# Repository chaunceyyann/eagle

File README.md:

EAGLE
=====
All my eagle projects and libraries can be found here.

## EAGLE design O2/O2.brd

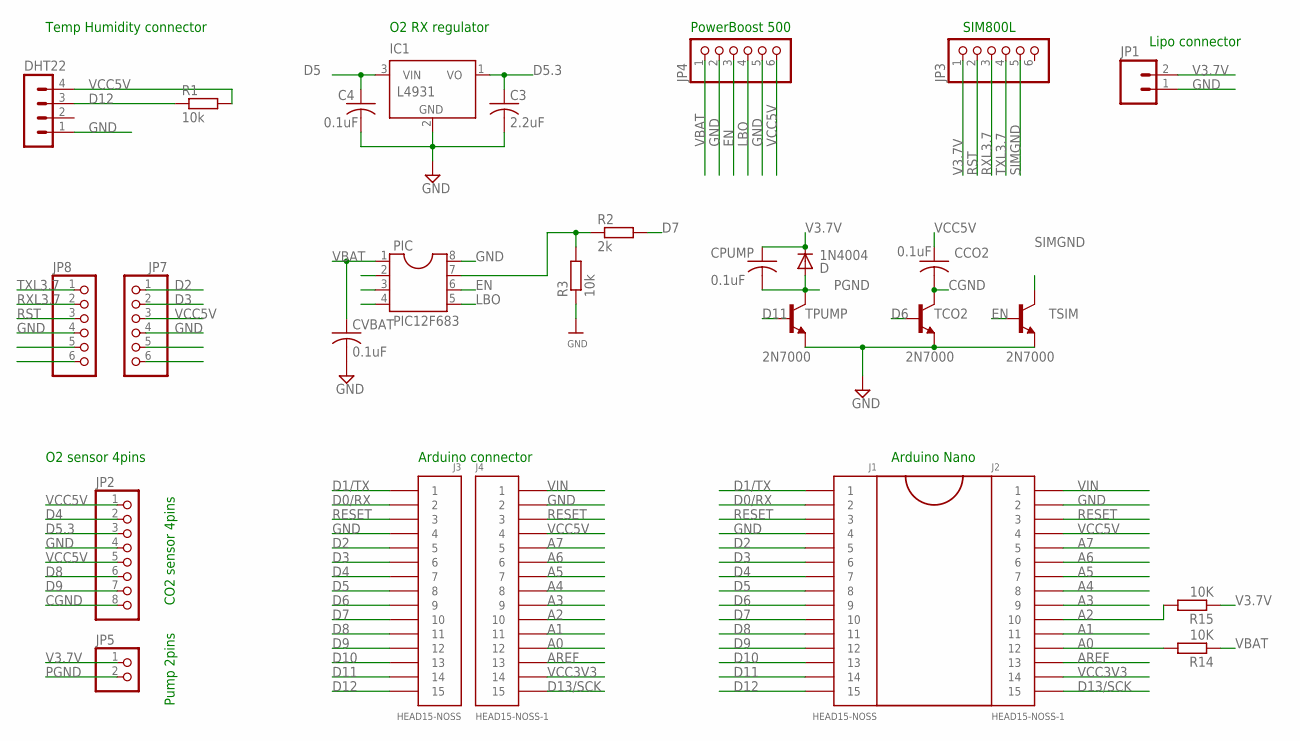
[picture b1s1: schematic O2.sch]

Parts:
C3: 2.2uF; C025-030X050
C4: 0.1uF; C025-030X050
CCO2: 0.1uF; C025-030X050
CPUMP: 0.1uF; C025-030X050
CVBAT: 0.1uF; C025-030X050
D: 1N4004; DO41-10
DHT22: MA04-1
IC1: L4931; TO92
J1, J3: HEAD15-NOSS
J2, J4: HEAD15-NOSS-1
JP1: M023.5MM; SCREWTERMINAL-3.5MM-2
JP2: PINHD-1X8BIG; 1X08-BIG
JP3, JP4, JP7, JP8: PINHD-1X6CB; 1X06-CLEANBIG
JP5: PINHD-1X2; 1X02
PIC: PIC12F683; SOCKET-08
R1, R3: 10k; 0204/5
R2: 2k; 0204/5
R14, R15: 10K; 0204/5
TCO2: 2N7000; TO92-EBC-OVAL
TPUMP: 2N7000; TO92-EBC-OVAL
TSIM: 2N7000; TO92-EBC-OVAL

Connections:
A0: J2.12, J4.12, R14.2
A1: J2.11, J4.11
A2: J2.10, J4.10, R15.2
A3: J2.9, J4.9
A4: J2.8, J4.8
A5: J2.7, J4.7
A6: J2.6, J4.6
A7: J2.5, J4.5
AREF: J2.13, J4.13
CGND: CCO2.2, JP2.8, TCO2.C
D0/RX: J1.2, J3.2
D1/TX: J1.1, J3.1
D2: J1.5, J3.5, JP7.1
D3: J1.6, J3.6, JP7.2
D4: J1.7, J3.7, JP2.2
D5: C4.1, IC1.3 (VIN), J1.8, J3.8
D5.3: C3.1, IC1.1 (VO), JP2.3
D6: J1.9, J3.9, TCO2.B
D7: J1.10, J3.10, R2.2
D8: J1.11, J3.11, JP2.6
D9: J1.12, J3.12, JP2.7
D10: J1.13, J3.13
D11: J1.14, J3.14, TPUMP.B
D12: DHT22.3, J1.15, J3.15, R1.1
D13/SCK: J2.15, J4.15
EN: JP4.3, PIC.6, TSIM.B
GND: C3.2, C4.2, CVBAT.2, DHT22.1, IC1.2 (GND), J1.4, J2.2, J3.4, J4.2, JP1.1, JP2.4, JP4.2, JP4.5, JP7.4, JP8.4, PIC.8, R3.1, TCO2.E, TPUMP.E, TSIM.E
LBO: JP4.4, PIC.5
unnamed: PIC.7, R2.1, R3.2
PGND: CPUMP.2, D.A, JP5.2, TPUMP.C
RESET: J1.3, J2.3, J3.3, J4.3
RST: JP3.2, JP8.3
RXL3.7: JP3.3, JP8.2
SIMGND: JP3.5, TSIM.C
TXL3.7: JP3.4, JP8.1
V3.7V: CPUMP.1, D.C, JP1.2, JP3.1, JP5.1, R15.1
VBAT: CVBAT.1, JP4.1, PIC.1, R14.1
VCC3V3: J2.14, J4.14
VCC5V: CCO2.1, DHT22.4, J2.4, J4.4, JP2.1, JP2.5, JP4.6, JP7.3, R1.2
VIN: J2.1, J4.1

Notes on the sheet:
O2 RX regulator
O2 sensor 4pins
Temp Humidity connector
Lipo connector
PowerBoost 500
Arduino Nano
Arduino connector
Pump 2pins
CO2 sensor 4pins
SIM800L

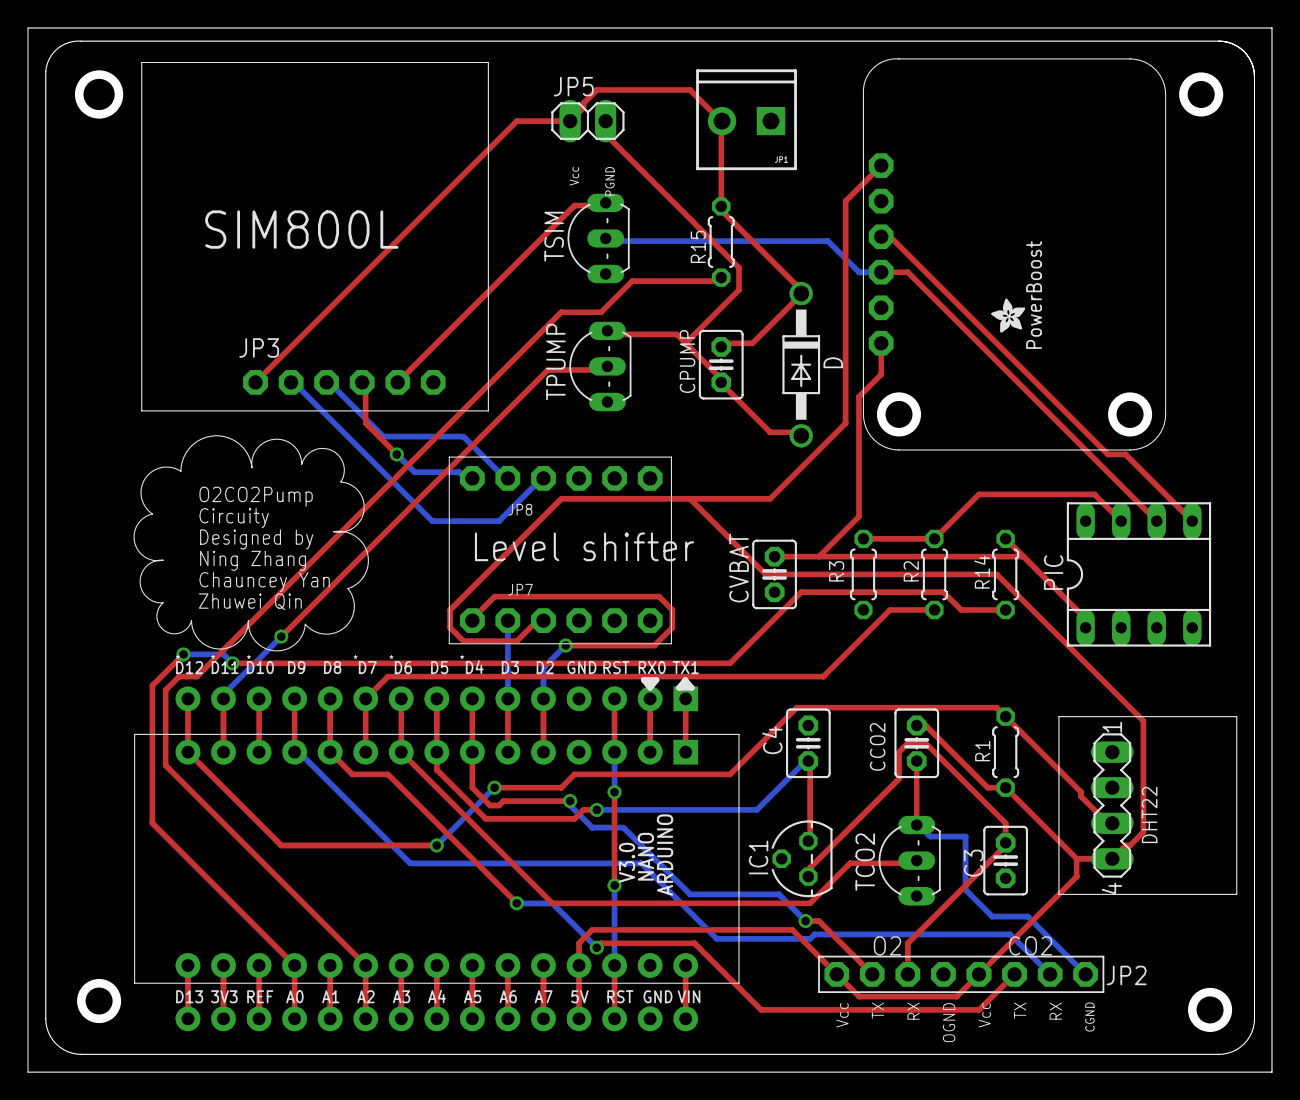
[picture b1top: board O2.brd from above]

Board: 2 copper layers, 88.9 x 74.6 mm, 29 parts (0 on the bottom side), 40 nets.

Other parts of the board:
U$34: ADAFRUIT_2.5MM

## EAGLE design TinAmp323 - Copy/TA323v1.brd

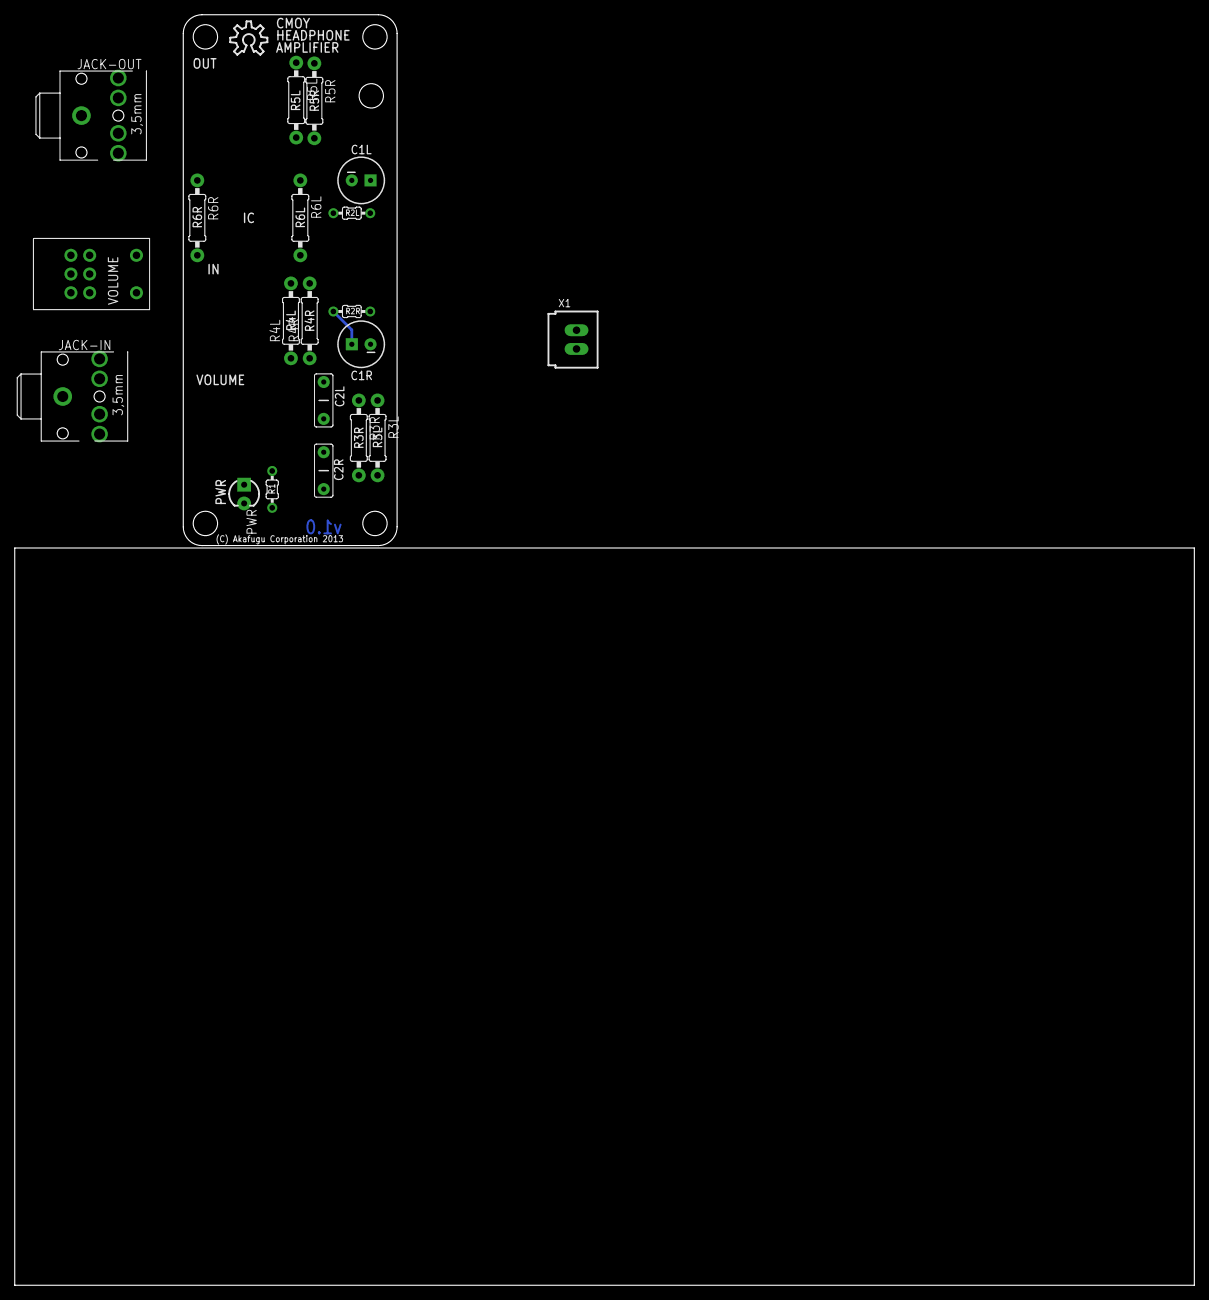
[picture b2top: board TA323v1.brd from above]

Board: 2 copper layers, 160.0 x 172.3 mm, 26 parts (0 on the bottom side), 15 nets.

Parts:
C1L, C1R: 220uF; CPOL-RADIAL-6.3MM
C2L, C2R: 0.1uF; CAP-PTH-VIMA-MKS2C031001A00KSSD
JACK-IN: STEREOJACK; STX3100
JACK-OUT: STEREOJACK; STX3100
JP1, JP2, JP3, JP4, JP5: STAND-OFF
PWR: LED3MM-MINUS
R1: 10k; 1/6W-RES-OUTLINE
R2L, R2R: 4.7k; 1/6W-RES-OUTLINE
R3L, R3R: 100k; 1/4W-RES-OUTLINE
R4L, R4R: 2k; 1/4W-RES-OUTLINE
R5L, R5R: 10k; 1/4W-RES-OUTLINE
R6L, R6R: 47R; 1/4W-RES-OUTLINE
U$1: OSHW-LOGO-OUTLINE
VOLUME: 10k; ALPS_RK0971221Z0X
X1: C-GRID-02-70543; 70543-02

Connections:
+9V: C1R.1, R1.2, R2R.2, VOLUME.S2
GND: C1L.2, JACK-IN.1, JACK-OUT.1, PWR.K, R2L.1, R3L.P$1, R3R.P$1, R4L.P$1, R4R.P$1, VOLUME.G1, VOLUME.G2, X1.1
INPUT-L: JACK-IN.2, VOLUME.I1
INPUT-R: JACK-IN.5, VOLUME.I2
L+: C2L.2, R3L.P$2
L-: R4L.P$2, R5L.P$2
unnamed: PWR.A, R1.1
unnamed: VOLUME.S1, X1.2
unnamed: C1L.1, C1R.2, R2L.2, R2R.1
OUTPUT-L: JACK-OUT.2, R5L.P$1, R6L.P$1
OUTPUT-R: JACK-OUT.5, R5R.P$1, R6R.P$1
R+: C2R.2, R3R.P$2
R-: R4R.P$2, R5R.P$2
VOLUME-OUT-L: C2L.1, VOLUME.O1
VOLUME-OUT-R: C2R.1, VOLUME.O2

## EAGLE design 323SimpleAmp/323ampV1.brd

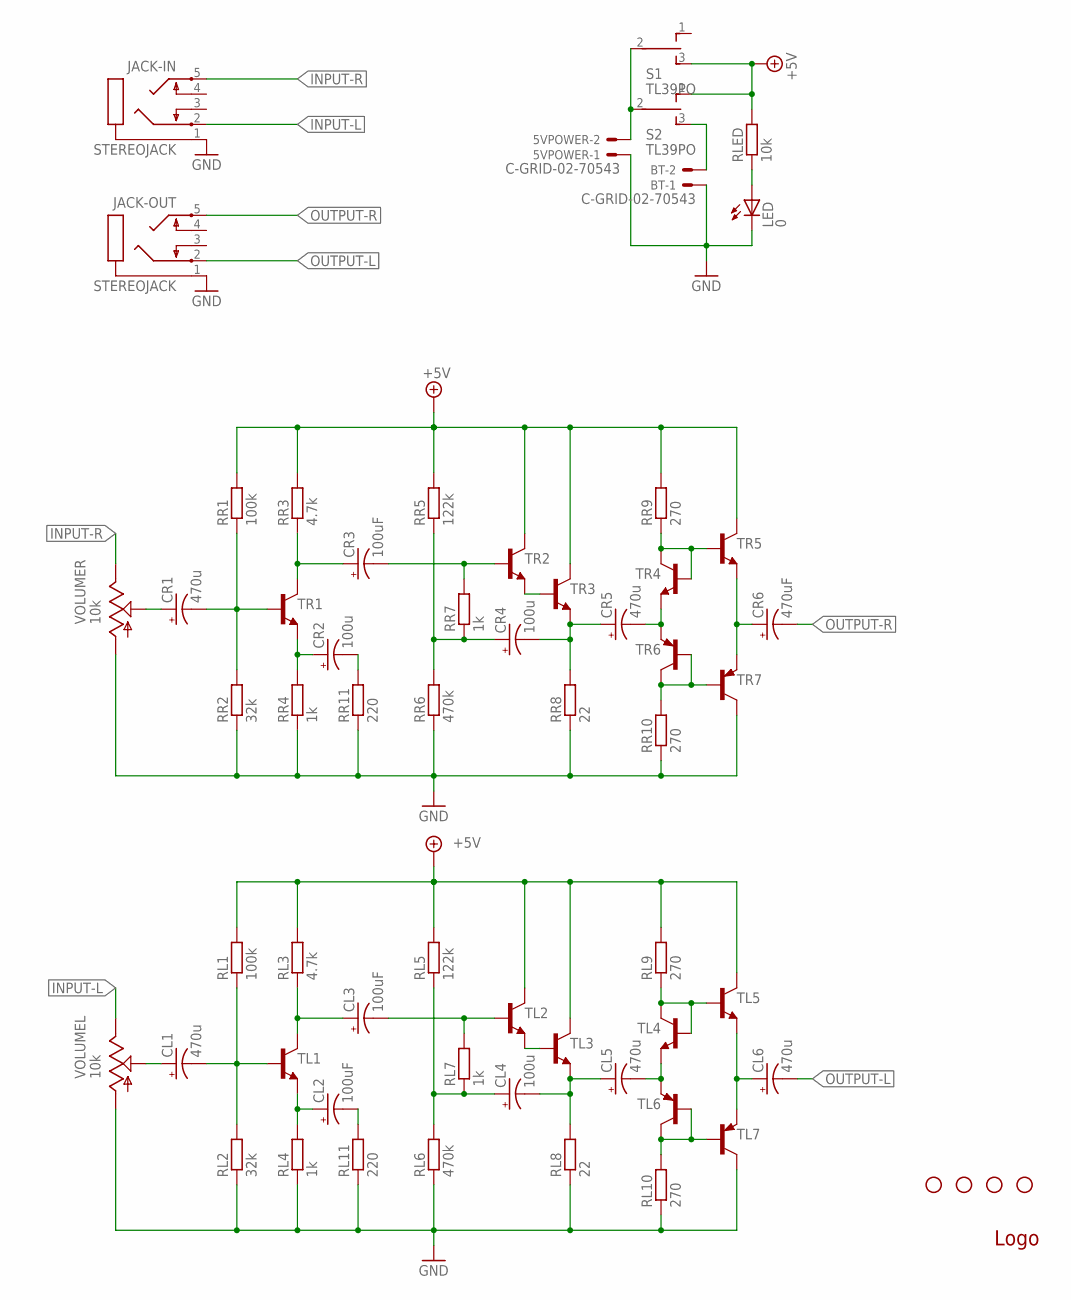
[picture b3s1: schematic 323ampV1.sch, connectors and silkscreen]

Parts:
5VPOWER: C-GRID-02-70543; 70543-02
BT: C-GRID-02-70543; 70543-02
CL1, CL5, CL6: 470u; E2,5-6
CL2, CL3: 100uF; E2,5-6
CL4: 100u; E2,5-6
CR1, CR5: 470u; E2,5-6
CR2, CR4: 100u; E2,5-6
CR3: 100uF; E2,5-6
CR6: 470uF; E2,5-6
JACK-IN: STEREOJACK; STX3100
JACK-OUT: STEREOJACK; STX3100
JP2, JP3, JP4, JP5: STAND-OFF
LED: 0; LED3MM-MINUS
RL1: 100k; 0204/7
RL2: 32k; 0204/7
RL3: 4.7k; 0204/7
RL4, RL7: 1k; 0204/7
RL5: 122k; 0204/7
RL6: 470k; 0204/7
RL8: 22; 0204/7
RL9, RL10: 270; 0204/7
RL11: 220; 0204/7
RLED: 10k; 0204/7
RR1: 100k; 0204/7
RR2: 32k; 0204/7
RR3: 4.7k; 0204/7
RR4, RR7: 1k; 0204/7
RR5: 122k; 0204/7
RR6: 470k; 0204/7
RR8: 22; 0204/7
RR9, RR10: 270; 0204/7
RR11: 220; 0204/7
S1, S2: TL39PO; TL3XPO
TL1, TL2, TL3, TL4, TL5: 2N4401-NPN-TO92-EBC; TO92-EBC
TL6, TL7: 2N4403-PNP-TO92-EBC; TO92-EBC
TR1, TR2, TR3, TR4, TR5: 2N4401-NPN-TO92-EBC; TO92-EBC
TR6, TR7: 2N4403-PNP-TO92-EBC; TO92-EBC
U$1: OSHW-LOGO-OUTLINE
VOLUME: 10k; ALPS_RK0971221Z0X

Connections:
+5V: RL1.2, RL3.2, RL5.2, RL9.2, RLED.2, RR1.2, RR3.2, RR5.2, RR9.2, S1.3 (S), S2.1 (O), TL2.C, TL3.C, TL5.C, TR2.C, TR3.C, TR5.C
GND: 5VPOWER.1, BT.1, JACK-IN.1, JACK-OUT.1, LED.K (C), RL2.1, RL4.1, RL6.1, RL8.1, RL10.1, RL11.1, RR2.1, RR4.1, RR6.1, RR8.1, RR10.1, RR11.1, TL7.C, TR7.C, VOLUME.G1 (1), VOLUME.G2 (1)
INPUT-L: JACK-IN.2, VOLUME.I1 (3)
INPUT-R: JACK-IN.5, VOLUME.I2 (3)
unnamed: LED.A, RLED.1
unnamed: 5VPOWER.2, S1.2, S2.2
unnamed: TR2.E, TR3.B
unnamed: CR3.+, RR3.1, TR1.C
unnamed: RL9.1, TL4.B, TL4.C, TL5.B
unnamed: CL5.-, TL4.E, TL6.E
unnamed: RL10.2, TL6.B, TL6.C, TL7.B
unnamed: CL6.+, TL5.E, TL7.E
unnamed: CL4.-, CL5.+, RL8.2, TL3.E
unnamed: CL4.+, RL5.1, RL6.2, RL7.1
unnamed: CL3.-, RL7.2, TL2.B
unnamed: CL2.-, RL11.2
unnamed: CL2.+, RL4.2, TL1.E
unnamed: CL1.+, VOLUME.O1 (2)
unnamed: TL2.E, TL3.B
unnamed: CL3.+, RL3.1, TL1.C
unnamed: BT.2, S2.3 (S)
unnamed: RR9.1, TR4.B, TR4.C, TR5.B
unnamed: CR5.-, TR4.E, TR6.E
unnamed: RR10.2, TR6.B, TR6.C, TR7.B
unnamed: CR6.+, TR5.E, TR7.E
unnamed: CR4.-, CR5.+, RR8.2, TR3.E
unnamed: CR4.+, RR5.1, RR6.2, RR7.1
unnamed: CR3.-, RR7.2, TR2.B
unnamed: CR2.-, RR11.2
unnamed: CR2.+, RR4.2, TR1.E
unnamed: CR1.+, VOLUME.O2 (2)
OUTPUT-L: CL6.-, JACK-OUT.2
OUTPUT-R: CR6.-, JACK-OUT.5
R+: CR1.-, RR1.1, RR2.2, TR1.B
R+1: CL1.-, RL1.1, RL2.2, TL1.B
S1: VOLUME.S1
S2: VOLUME.S2

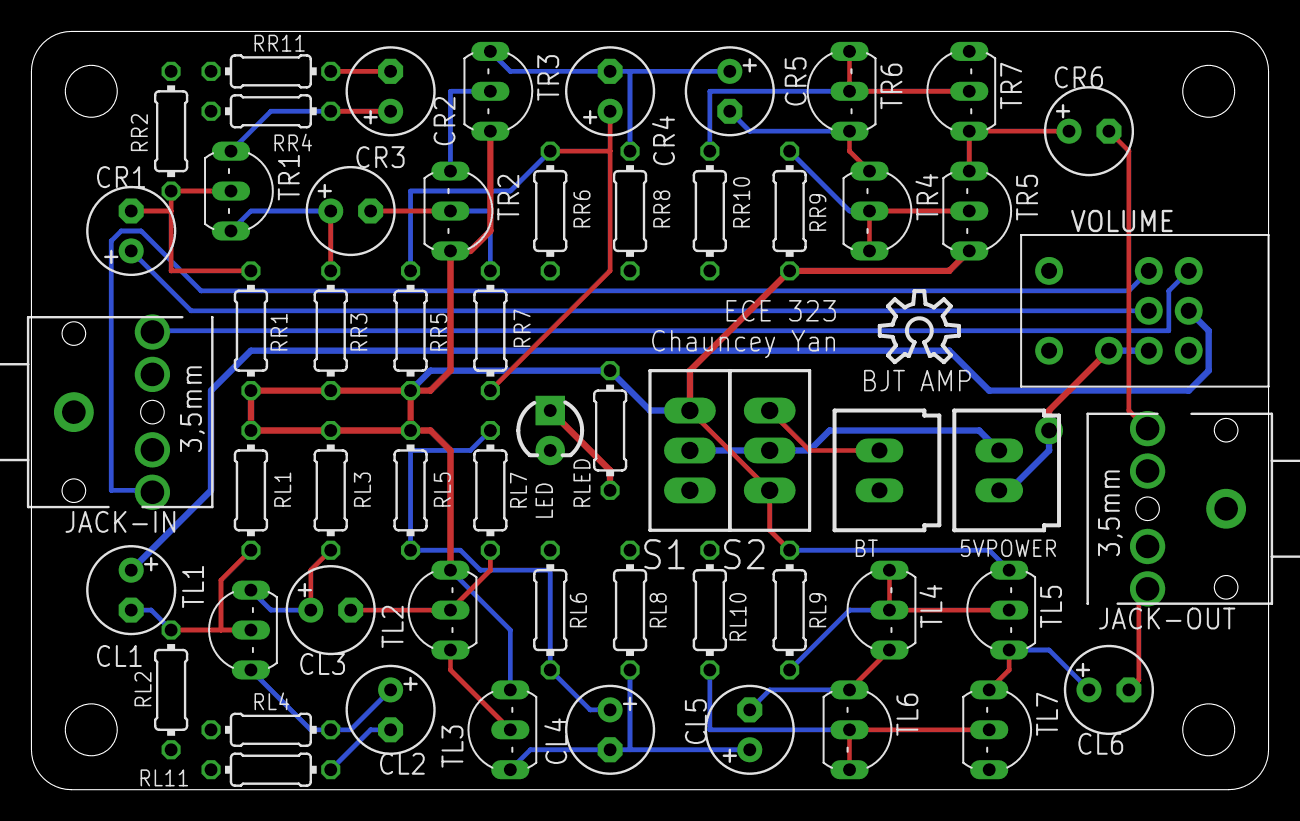
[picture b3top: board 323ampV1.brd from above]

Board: 2 copper layers, 78.7 x 48.3 mm, 62 parts (0 on the bottom side), 35 nets.

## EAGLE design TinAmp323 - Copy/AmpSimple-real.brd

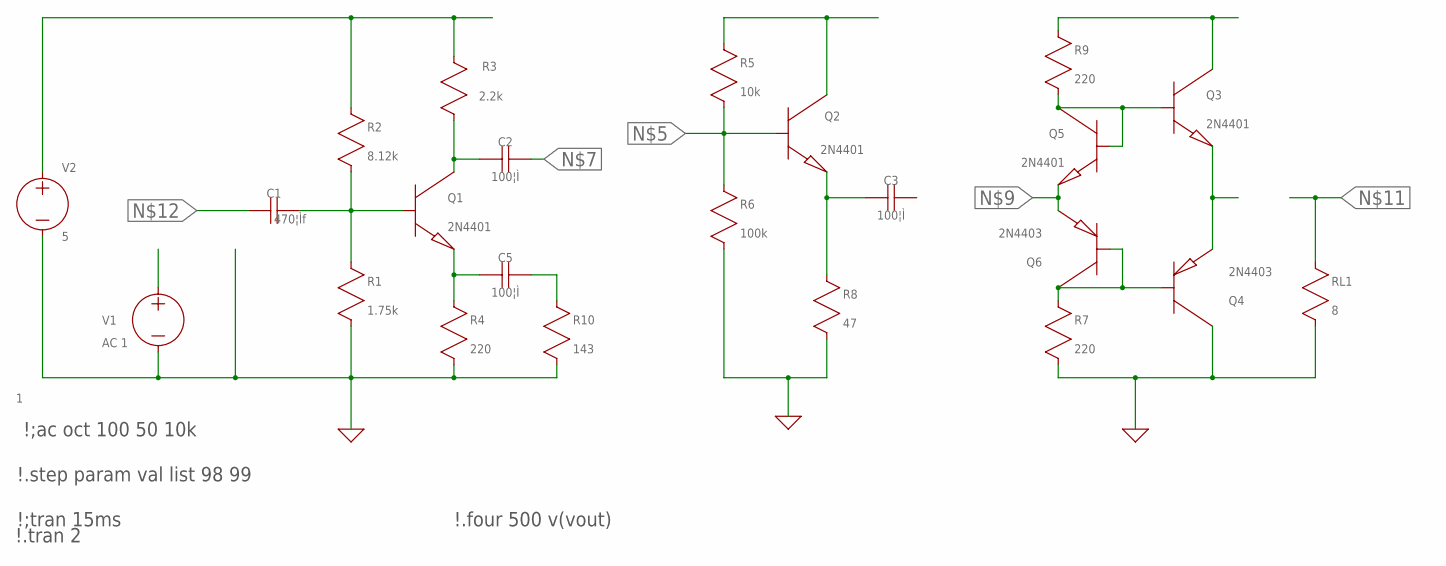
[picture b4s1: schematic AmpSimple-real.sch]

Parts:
C1: 470¦Ìf; C0805
C2, C3, C5: 100¦Ì; C0805
Q1, Q2, Q3, Q5: 2N4401; SOT23
Q4, Q6: 2N4403; SOT23
R1: 1.75k; R0805
R2: 8.12k; R0805
R3: 2.2k; R0805
R4, R7, R9: 220; R0805
R5: 10k; R0805
R6: 100k; R0805
R8: 47; R0805
R10: 143; R0805
RL1: 8; R0805

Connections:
0: Q4.3 (C), R1.2 (B), R4.2 (B), R6.2 (B), R7.2 (B), R8.2 (B), R10.2 (B), RL1.2 (B)
unnamed: R2.1 (A), R3.1 (A)
unnamed: Q2.3 (C), R5.1 (A)
unnamed: Q3.3 (C), R9.1 (A)
unnamed: Q3.2 (B), Q5.2 (B), Q5.3 (C), R9.2 (B)
unnamed: Q2.2 (B), R5.2 (B), R6.1 (A)
unnamed: C2.2 (B), Q1.3 (C), R3.2 (B)
unnamed: C3.2 (B), Q2.1 (E), R8.1 (A)
unnamed: Q5.1 (E), Q6.1 (E)
unnamed: Q3.1 (E), Q4.1 (E)
unnamed: C1.1 (A), Q1.2 (B), R1.1 (A), R2.2 (B)
unnamed: Q4.2 (B), Q6.2 (B), Q6.3 (C), R7.1 (A)
unnamed: C5.2 (B), Q1.1 (E), R4.1 (A)
unnamed: C5.1 (A), R10.1 (A)

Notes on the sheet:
\!.step param val list 98 99
\!;tran 15ms
\!;ac oct 100 50 10k
\!.four 500 v(vout)
\!.tran 2

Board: 2 copper layers, 21 parts (0 on the bottom side), 14 nets, no tracks yet.

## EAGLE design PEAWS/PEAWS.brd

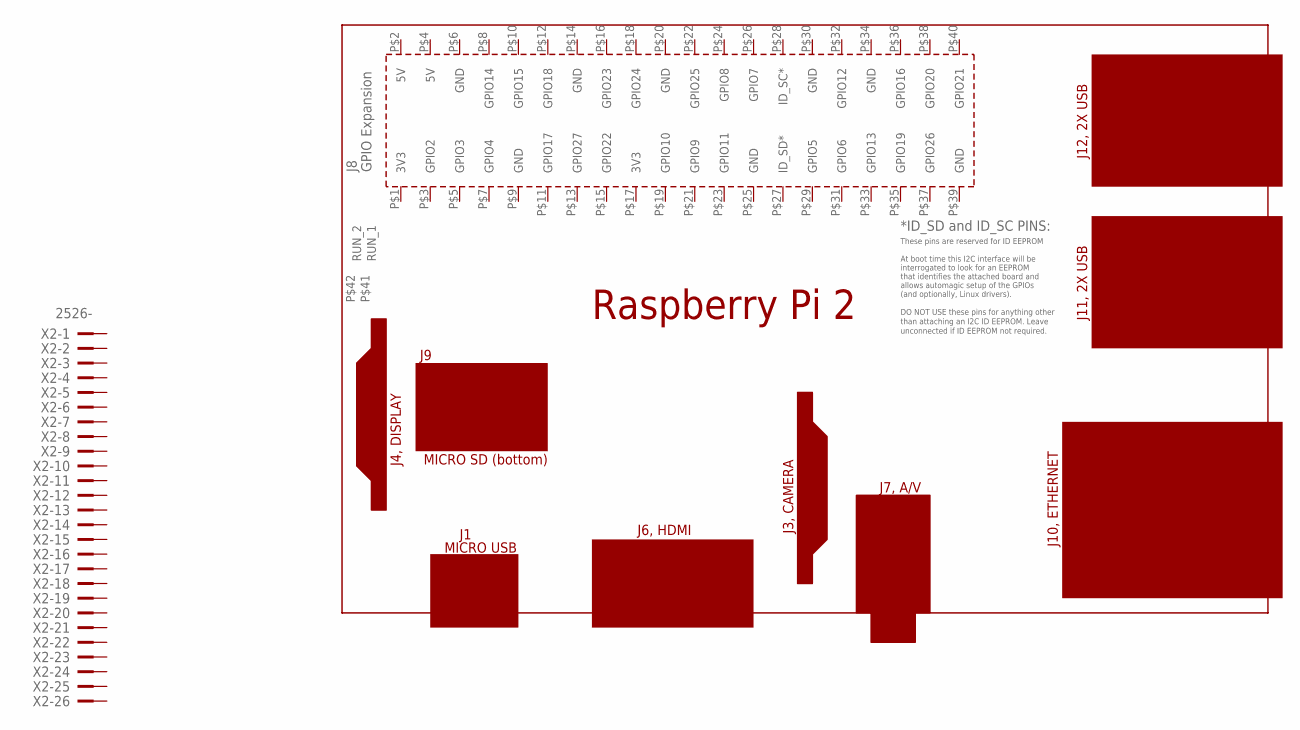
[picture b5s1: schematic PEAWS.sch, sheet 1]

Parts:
PCB1: RPI2
X2: 2526-; PAK100/2500-26

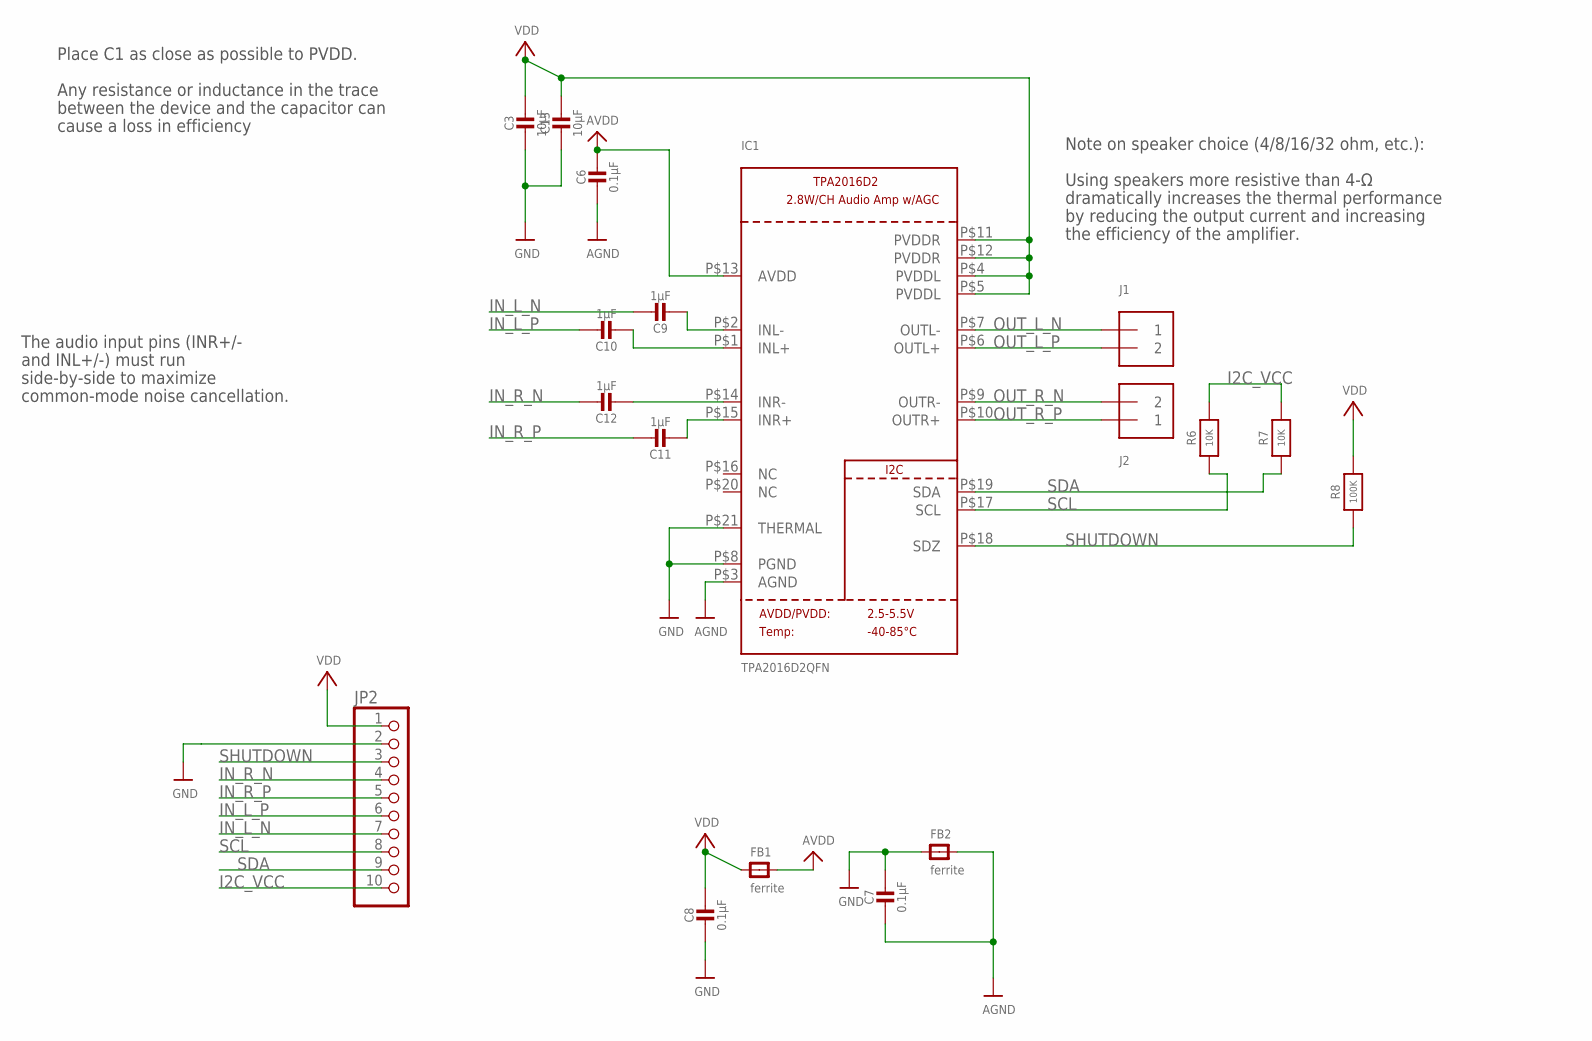
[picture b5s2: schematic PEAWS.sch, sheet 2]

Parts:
C3, C13: 10µF; 0805-NO
C6, C7, C8: 0.1µF; 0805-NO
C9, C10, C11, C12: 1µF; 0805-NO
FB1, FB2: ferrite; _0805MP
IC1: TPA2016D2QFN; QFN20_4MM
J1, J2: TERMBLOCK_1X2; TERMBLOCK_1X2-3.5MM
JP2: HEADER-1X1070MIL; 1X10_ROUND70
R6, R7: 10K; 0805-NO
R8: 100K; 0805-NO

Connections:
AGND: C6.2, C7.2, FB2.2, IC1.P$3 (AGND)
AVDD: C6.1, FB1.2, IC1.P$13 (AVDD)
GND: C3.2, C7.1, C8.2, C13.2, FB2.1, IC1.P$8 (PGND), IC1.P$21 (THERMAL), JP2.2; also elsewhere on the board
I2C_VCC: JP2.10, R6.2, R7.2
IN_L_N: C9.1, JP2.7
IN_L_P: C10.1, JP2.6
IN_R_N: C12.1, JP2.4
IN_R_P: C11.1, JP2.5
unnamed: C10.2, IC1.P$1 (INL+)
unnamed: C9.2, IC1.P$2 (INL-)
unnamed: C12.2, IC1.P$14 (INR-)
unnamed: C11.2, IC1.P$15 (INR+)
OUT_L_N: IC1.P$7 (OUTL-), J1.1
OUT_L_P: IC1.P$6 (OUTL+), J1.2
OUT_R_N: IC1.P$9 (OUTR-), J2.2
OUT_R_P: IC1.P$10 (OUTR+), J2.1
SCL: IC1.P$17 (SCL), JP2.8, R6.1
SDA: IC1.P$19 (SDA), JP2.9, R7.1
SHUTDOWN: IC1.P$18 (SDZ), JP2.3, R8.1
VDD: C3.1, C8.1, C13.1, FB1.1, IC1.P$4 (PVDDL), IC1.P$5 (PVDDL), IC1.P$11 (PVDDR), IC1.P$12 (PVDDR), JP2.1, R8.2; also elsewhere on the board

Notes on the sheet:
Place C1 as close as possible to PVDD.
Any resistance or inductance in the trace
between the device and the capacitor can
cause a loss in efficiency
Using speakers more resistive than 4-Ω
dramatically increases the thermal performance
by reducing the output current and increasing
the efficiency of the amplifier.
Note on speaker choice (4/8/16/32 ohm, etc.):
The audio input pins (INR+/-
and INL+/-) must run
side-by-side to maximize
common-mode noise cancellation.

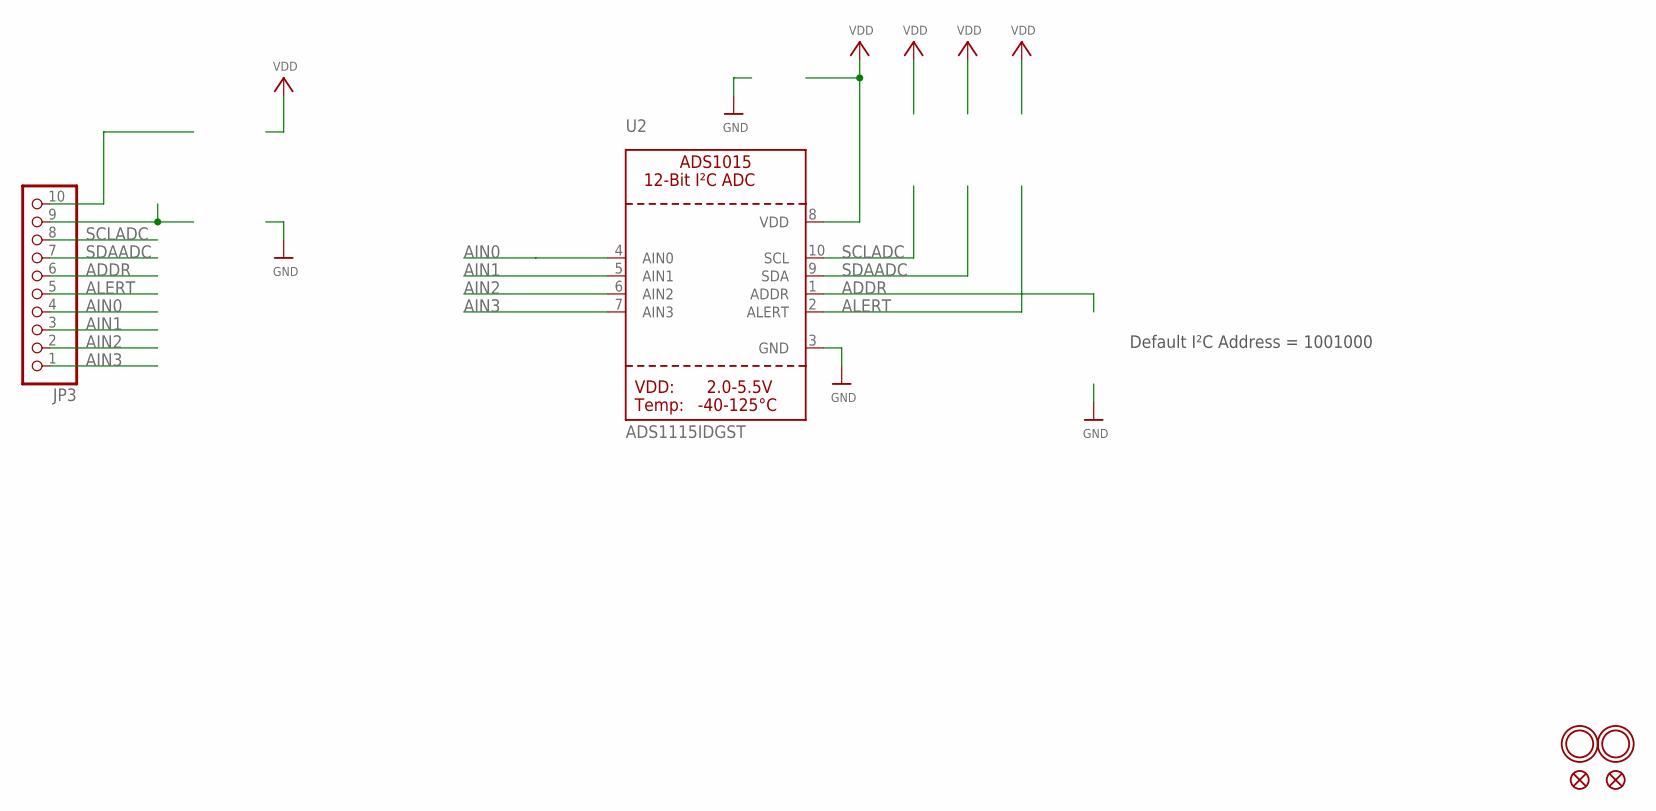
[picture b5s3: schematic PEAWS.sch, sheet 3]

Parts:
FID1, FID2: FIDUCIAL""; FIDUCIAL_1MM
JP3: HEADER-1X1070MIL; 1X10_ROUND70
U2: ADS1115IDGST; MSOP10
U$55, U$56: MOUNTINGHOLE2.5; MOUNTINGHOLE_2.5_PLATED

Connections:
ADDR: JP3.6, U2.1 (ADDR)
AIN0: JP3.4, U2.4 (AIN0)
AIN1: JP3.3, U2.5 (AIN1)
AIN2: JP3.2, U2.6 (AIN2)
AIN3: JP3.1, U2.7 (AIN3)
ALERT: JP3.5, U2.2 (ALERT)
GND: U2.3 (GND); also elsewhere on the board
SCLADC: JP3.8, U2.10 (SCL)
SDAADC: JP3.7, U2.9 (SDA)
VDD: U2.8 (VDD); also elsewhere on the board

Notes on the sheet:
Default I²C Address = 1001000

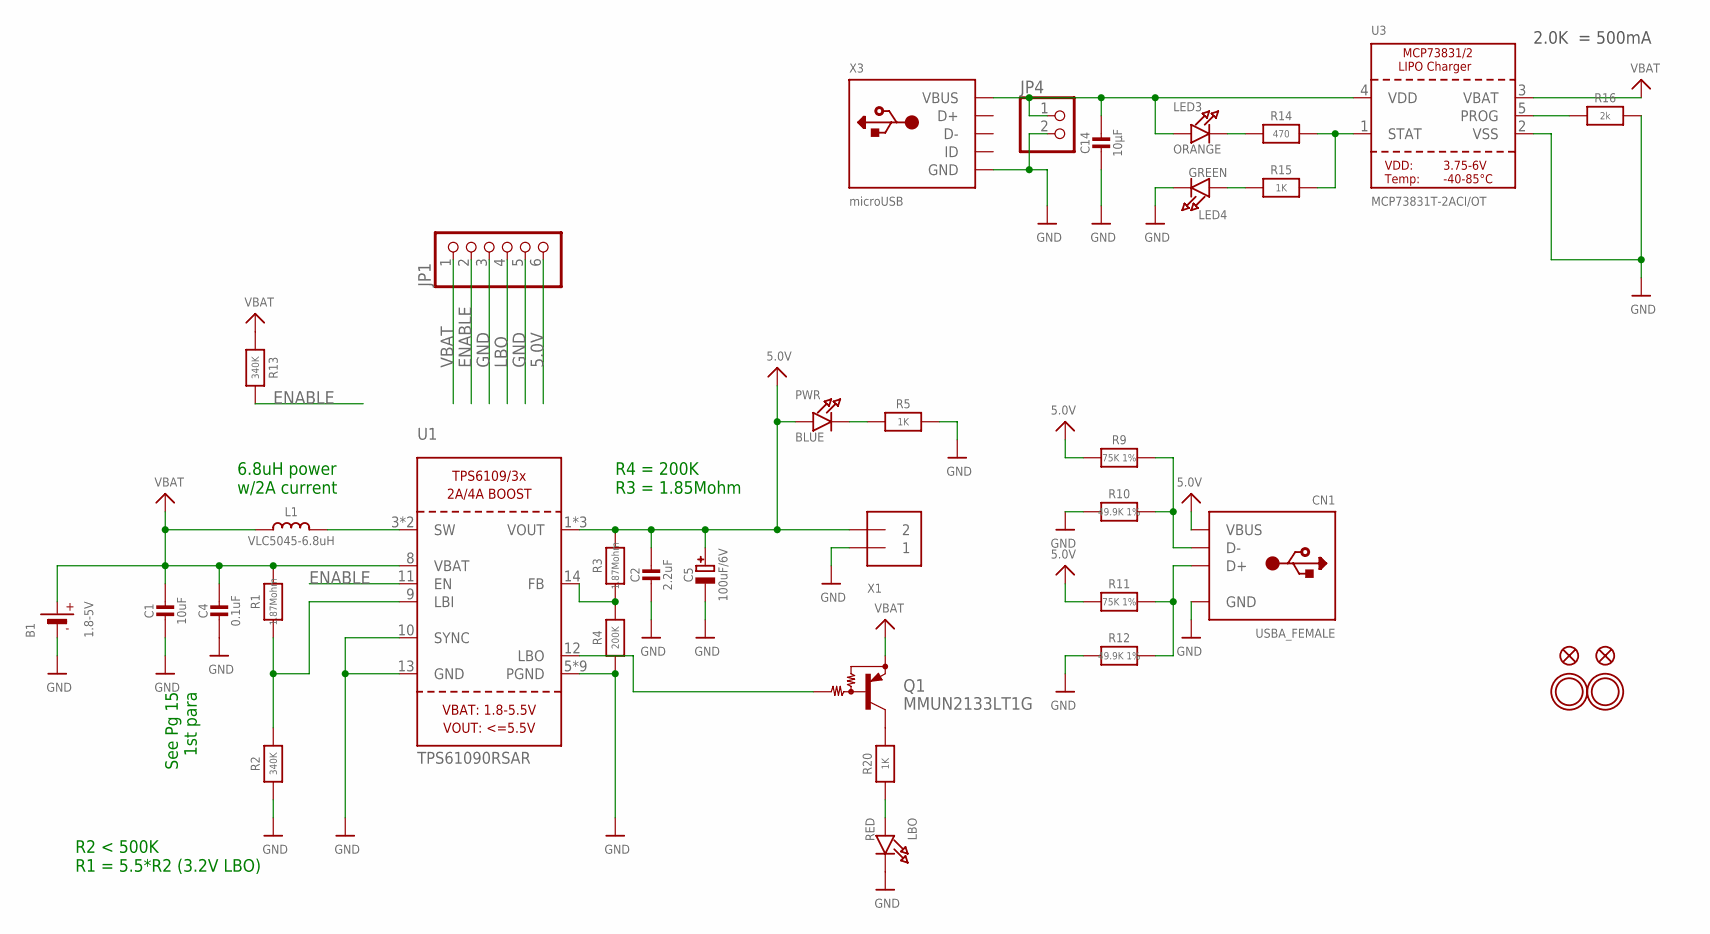
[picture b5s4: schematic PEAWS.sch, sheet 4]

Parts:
B1: 1.8-5V; JSTPH2
C1: 10uF; 0805-NO
C2: 2.2uF; 0805-NO
C4: 0.1uF; 0805-NO
C5: 100uF/6V; EIA3528-21/B-R
C14: 10µF; 0805-NO
CN1: USBA_FEMALE; USB_HOST-PTH
FID3, FID4: FIDUCIAL""; FIDUCIAL_1MM
JP1: PINHD-1X6CB; 1X06-CLEANBIG
JP4: HEADER-1X2ROUND; 1X02_ROUND
L1: VLC5045-6.8uH; INDUCTOR_5X5MM_TDK_VLC5045
LBO: RED; CHIPLED_0805_NOOUTLINE
LED3: ORANGE; CHIPLED_0805_NOOUTLINE
LED4: GREEN; CHIPLED_0805_NOOUTLINE
PWR: BLUE; CHIPLED_0805_NOOUTLINE
Q1: MMUN2133LT1G; SC59-BEC
R1, R3: 1.87Mohm; 0805-NO
R2, R13: 340K; 0805-NO
R4: 200K; 0805-NO
R5, R15, R20: 1K; 0805-NO
R9, R11: 75K 1%; 0805-NO
R10, R12: 49.9K 1%; 0805-NO
R14: 470; 0805-NO
R16: 2k; 0805-NO
U1: TPS61090RSAR; PVQFN-16
U3: MCP73831T-2ACI/OT; SOT23-5
U$3, U$6: MOUNTINGHOLE2.5; MOUNTINGHOLE_2.5_PLATED
X1: TERMBLOCK_1X2; TERMBLOCK_1X2-3.5MM
X3: microUSB; 4UCONN_20329

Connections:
5.0V: C2.1, C5.+, CN1.VBUS, JP1.6, PWR.A, R3.2, R9.2, R11.2, U1.1 (VOUT), U1.15 (VOUT), U1.16 (VOUT), X1.2
D+: CN1.D+, R11.1, R12.1
D-: CN1.D-, R9.1, R10.1
ENABLE: JP1.2, R13.2, U1.11 (EN)
GND: B1.1 (-), C1.2, C2.2, C4.2, C5.-, C14.2, CN1.GND, JP1.3, JP1.5, JP4.2, LBO.C, LED4.C, R2.1, R4.1, R5.2, R10.2, R12.2, R16.2, U1.5 (PGND), U1.6 (PGND), U1.7 (PGND), U1.10 (SYNC), U1.13 (GND), U1.P$18 (PGND), U1.P$19 (PGND), U1.P$20 (PGND), U1.P$21 (PGND), U1.P$22 (PGND), U1.THERMAL (PGND), U3.2 (VSS), X1.1, X3.BASE@1 (GND), X3.BASE@2 (GND), X3.GND, X3.SPRT@1 (GND), X3.SPRT@2 (GND), X3.SPRT@3 (GND), X3.SPRT@4 (GND); also elsewhere on the board
LBO: JP1.4, Q1.B, U1.12 (LBO)
unnamed: L1.P$2 (2), U1.3 (SW), U1.4 (SW)
unnamed: R1.1, R2.2, U1.9 (LBI)
unnamed: PWR.C, R5.1
unnamed: R3.1, R4.2, U1.14 (FB)
unnamed: LBO.A, R20.1
unnamed: Q1.C, R20.2
unnamed: LED3.C, R14.1
unnamed: R14.2, R15.2, U3.1 (STAT)
unnamed: R16.1, U3.5 (PROG)
unnamed: LED4.A, R15.1
VBAT: B1.2 (+), C1.1, C4.1, JP1.1, L1.P$1 (1), Q1.E, R1.2, R13.1, U1.8 (VBAT), U3.3 (VBAT)
VDD1: C14.1, JP4.1, LED3.A, U3.4 (VDD), X3.VBUS

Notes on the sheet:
See Pg 15 1st para
6.8uH power w/2A current
R2 < 500K R1 = 5.5*R2 (3.2V LBO)
R4 = 200K R3 = 1.85Mohm
2.0K = 500mA

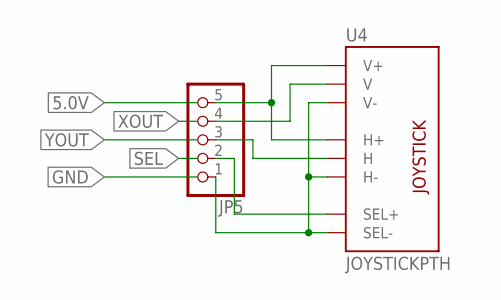
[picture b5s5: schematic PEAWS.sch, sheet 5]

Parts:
JP5: PINHD-1X5; 1X05
U4: JOYSTICKPTH; JOYSTICK

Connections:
unnamed: JP5.5, U4.H1 (H+), U4.V1 (V+)
unnamed: JP5.1, U4.B2A (SEL-), U4.H3 (H-), U4.V3 (V-)
unnamed: JP5.4, U4.V2 (V)
unnamed: JP5.3, U4.H2 (H)
unnamed: JP5.2, U4.B1A (SEL+)

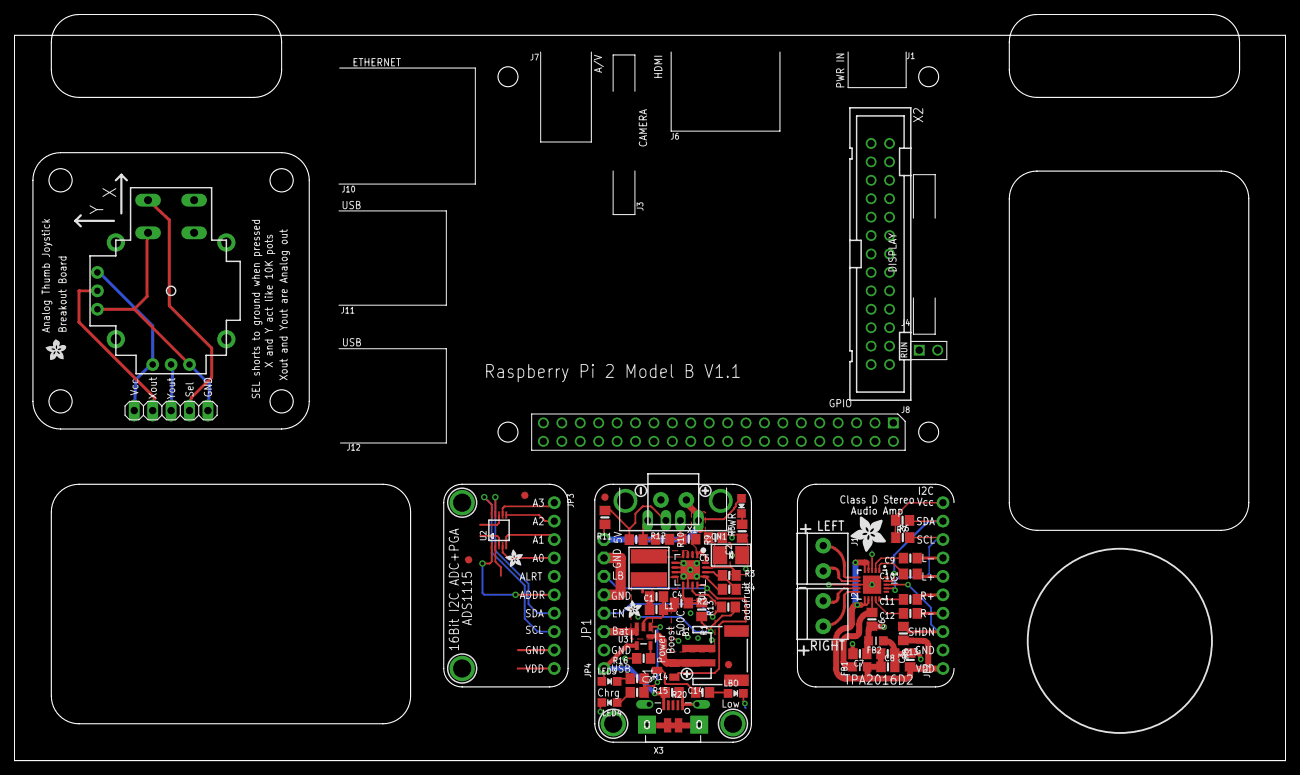
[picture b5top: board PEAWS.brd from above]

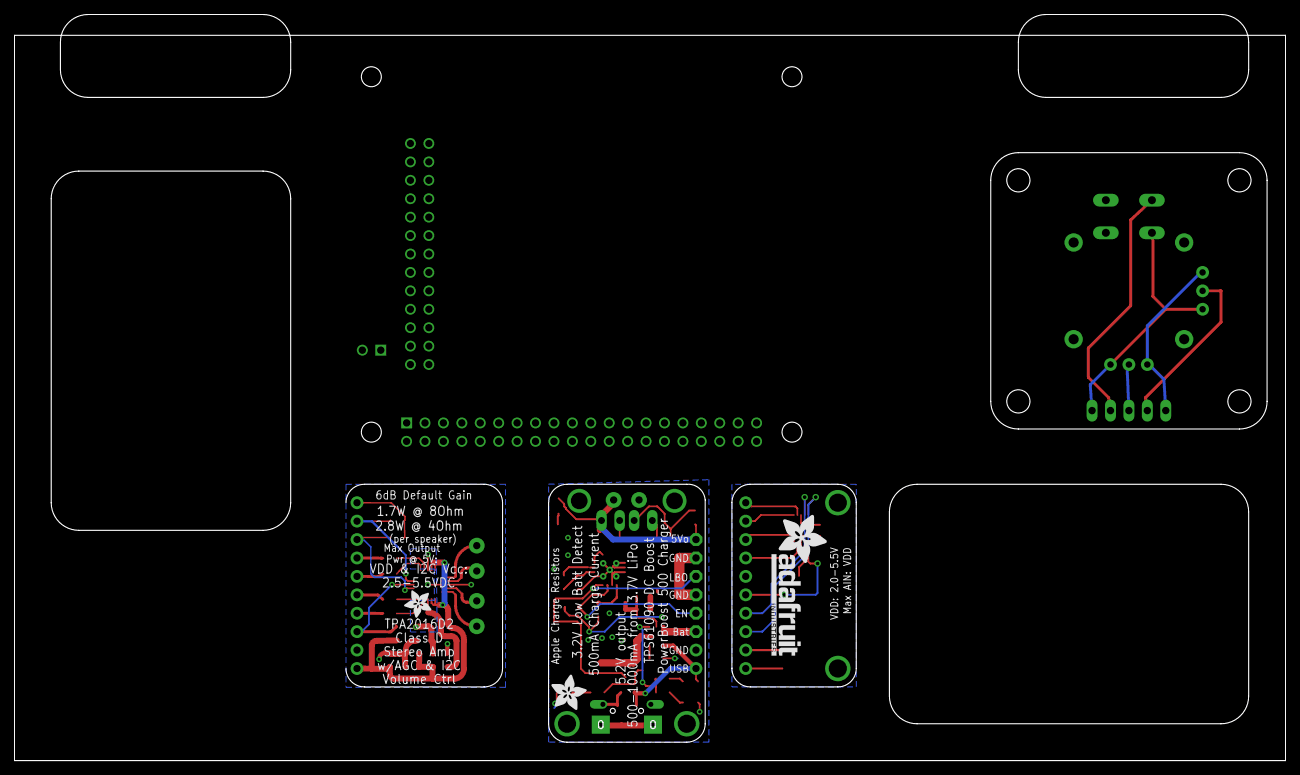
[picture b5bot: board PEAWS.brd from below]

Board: 2 copper layers, 175.2 x 102.9 mm, 75 parts (3 on the bottom side), 50 nets.

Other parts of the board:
U$13: ADAFRUIT200MIL
U$47, U$71: ADAFRUIT_5MM
U$48: ADAFRUIT_3.5MM
U$57: ADAFRUIT_TEXT_20MM
U$58, U$70: ADAFRUIT_2.5MM
U$67, U$68: SYMBOL_PLUS
U$69: SYMBOL_MINUS

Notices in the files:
parts and their libraries:
microbuilder: This work is placed in the public domain, and may be freely used for commercial and non-commercial work with the following conditions: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
SparkFun-Connectors: Licensing: Creative Commons ShareAlike 4.0 International - https://creativecommons.org/licenses/by-sa/4.0
